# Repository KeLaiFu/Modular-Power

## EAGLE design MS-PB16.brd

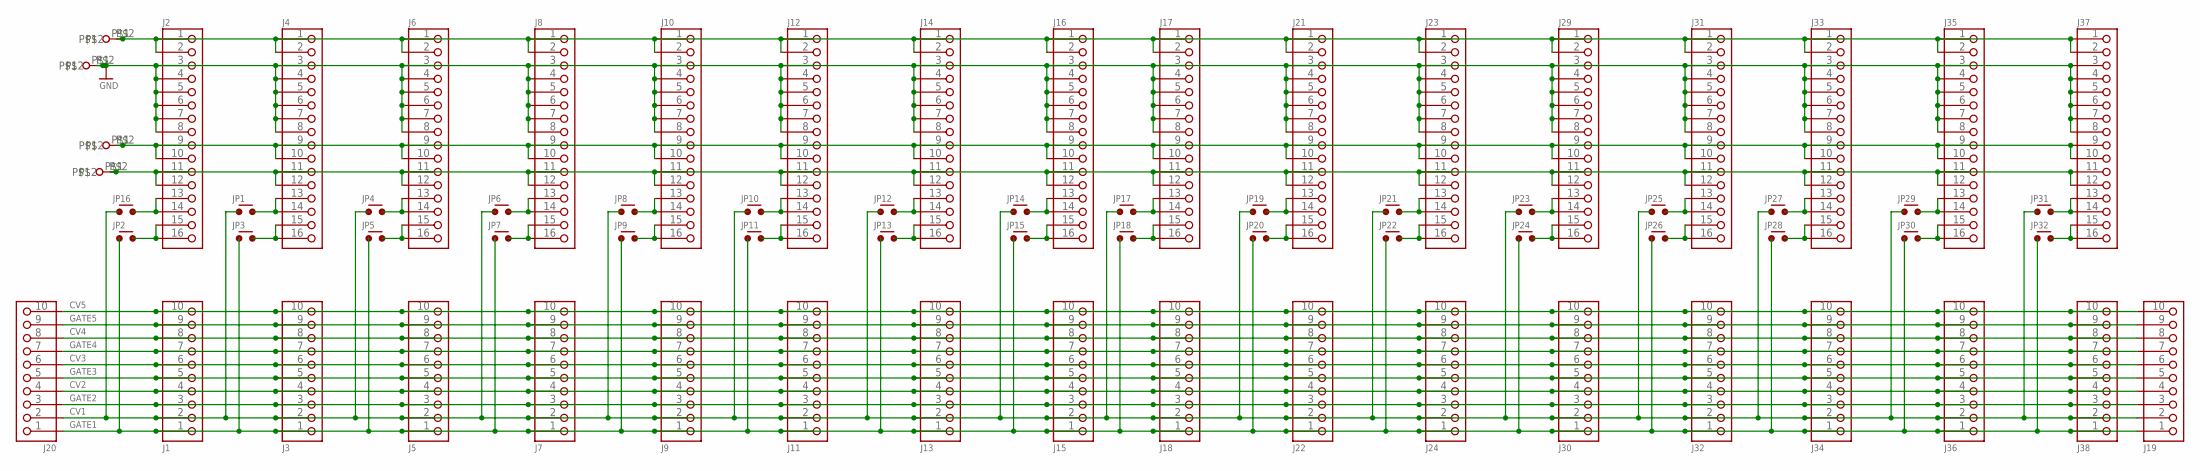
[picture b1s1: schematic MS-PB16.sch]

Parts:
J1, J3, J5, J7, J9, J11, J13, J15, J18, J19, J20, J22, J24, J30, J32, J34, J36, J38: CON10PD_S; PD10S
J2, J4, J6, J8, J10, J12, J14, J16, J17, J21, J23, J29, J31, J33, J35, J37: CON16_PDS; PD16S
J25, J26, J27, J28: FLACHSTECKER-6,35
JP1, JP2, JP3, JP4, JP5, JP6, JP7, JP8, JP9, JP10, JP11, JP12, JP13, JP14, JP15, JP16, JP17, JP18, JP19, JP20, JP21, JP22, JP23, JP24, JP25, JP26, JP27, JP28, JP29, JP30, JP31, JP32: JUMP2J2; JUMP2

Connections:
+5V: J2.11, J2.12, J4.11, J4.12, J6.11, J6.12, J8.11, J8.12, J10.11, J10.12, J12.11, J12.12, J14.11, J14.12, J16.11, J16.12, J17.11, J17.12, J21.11, J21.12, J23.11, J23.12, J27.P$1, J27.P$2, J29.11, J29.12, J31.11, J31.12, J33.11, J33.12, J35.11, J35.12, J37.11, J37.12
+12V: J2.9, J2.10, J4.9, J4.10, J6.9, J6.10, J8.9, J8.10, J10.9, J10.10, J12.9, J12.10, J14.9, J14.10, J16.9, J16.10, J17.9, J17.10, J21.9, J21.10, J23.9, J23.10, J26.P$1, J26.P$2, J29.9, J29.10, J31.9, J31.10, J33.9, J33.10, J35.9, J35.10, J37.9, J37.10
-12V: J2.1, J2.2, J4.1, J4.2, J6.1, J6.2, J8.1, J8.2, J10.1, J10.2, J12.1, J12.2, J14.1, J14.2, J16.1, J16.2, J17.1, J17.2, J21.1, J21.2, J23.1, J23.2, J25.P$1, J25.P$2, J29.1, J29.2, J31.1, J31.2, J33.1, J33.2, J35.1, J35.2, J37.1, J37.2
CV1: J1.2, J3.2, J5.2, J7.2, J9.2, J11.2, J13.2, J15.2, J18.2, J19.2, J20.2, J22.2, J24.2, J30.2, J32.2, J34.2, J36.2, J38.2, JP1.1, JP4.1, JP6.1, JP8.1, JP10.1, JP12.1, JP14.1, JP16.1, JP17.1, JP19.1, JP21.1, JP23.1, JP25.1, JP27.1, JP29.1, JP31.1
CV2: J1.4, J3.4, J5.4, J7.4, J9.4, J11.4, J13.4, J15.4, J18.4, J19.4, J20.4, J22.4, J24.4, J30.4, J32.4, J34.4, J36.4, J38.4
CV3: J1.6, J3.6, J5.6, J7.6, J9.6, J11.6, J13.6, J15.6, J18.6, J19.6, J20.6, J22.6, J24.6, J30.6, J32.6, J34.6, J36.6, J38.6
CV4: J1.8, J3.8, J5.8, J7.8, J9.8, J11.8, J13.8, J15.8, J18.8, J19.8, J20.8, J22.8, J24.8, J30.8, J32.8, J34.8, J36.8, J38.8
CV5: J1.10, J3.10, J5.10, J7.10, J9.10, J11.10, J13.10, J15.10, J18.10, J19.10, J20.10, J22.10, J24.10, J30.10, J32.10, J34.10, J36.10, J38.10
GATE1: J1.1, J3.1, J5.1, J7.1, J9.1, J11.1, J13.1, J15.1, J18.1, J19.1, J20.1, J22.1, J24.1, J30.1, J32.1, J34.1, J36.1, J38.1, JP2.1, JP3.1, JP5.1, JP7.1, JP9.1, JP11.1, JP13.1, JP15.1, JP18.1, JP20.1, JP22.1, JP24.1, JP26.1, JP28.1, JP30.1, JP32.1
GATE2: J1.3, J3.3, J5.3, J7.3, J9.3, J11.3, J13.3, J15.3, J18.3, J19.3, J20.3, J22.3, J24.3, J30.3, J32.3, J34.3, J36.3, J38.3
GATE3: J1.5, J3.5, J5.5, J7.5, J9.5, J11.5, J13.5, J15.5, J18.5, J19.5, J20.5, J22.5, J24.5, J30.5, J32.5, J34.5, J36.5, J38.5
GATE4: J1.7, J3.7, J5.7, J7.7, J9.7, J11.7, J13.7, J15.7, J18.7, J19.7, J20.7, J22.7, J24.7, J30.7, J32.7, J34.7, J36.7, J38.7
GATE5: J1.9, J3.9, J5.9, J7.9, J9.9, J11.9, J13.9, J15.9, J18.9, J19.9, J20.9, J22.9, J24.9, J30.9, J32.9, J34.9, J36.9, J38.9
GND: J2.3, J2.4, J2.5, J2.6, J2.7, J2.8, J4.3, J4.4, J4.5, J4.6, J4.7, J4.8, J6.3, J6.4, J6.5, J6.6, J6.7, J6.8, J8.3, J8.4, J8.5, J8.6, J8.7, J8.8, J10.3, J10.4, J10.5, J10.6, J10.7, J10.8, J12.3, J12.4, J12.5, J12.6, J12.7, J12.8, J14.3, J14.4, J14.5, J14.6, J14.7, J14.8, J16.3, J16.4, J16.5, J16.6, J16.7, J16.8, J17.3, J17.4, J17.5, J17.6, J17.7, J17.8, J21.3, J21.4, J21.5, J21.6, J21.7, J21.8, J23.3, J23.4, J23.5, J23.6, J23.7, J23.8, J28.P$1, J28.P$2, J29.3, J29.4, J29.5, J29.6, J29.7, J29.8, J31.3, J31.4, J31.5, J31.6, J31.7, J31.8, J33.3, J33.4, J33.5, J33.6, J33.7, J33.8, J35.3, J35.4, J35.5, J35.6, J35.7, J35.8, J37.3, J37.4, J37.5, J37.6, J37.7, J37.8
unnamed: J4.13, J4.14, JP1.2
unnamed: J2.15, J2.16, JP2.2
unnamed: J2.13, J2.14, JP16.2
unnamed: J4.15, J4.16, JP3.2
unnamed: J6.13, J6.14, JP4.2
unnamed: J6.15, J6.16, JP5.2
unnamed: J8.15, J8.16, JP7.2
unnamed: J8.13, J8.14, JP6.2
unnamed: J10.13, J10.14, JP8.2
unnamed: J10.15, J10.16, JP9.2
unnamed: J12.13, J12.14, JP10.2
unnamed: J12.15, J12.16, JP11.2
unnamed: J14.13, J14.14, JP12.2
unnamed: J14.15, J14.16, JP13.2
unnamed: J16.13, J16.14, JP14.2
unnamed: J16.15, J16.16, JP15.2
unnamed: J17.13, J17.14, JP17.2
unnamed: J17.15, J17.16, JP18.2
unnamed: J21.13, J21.14, JP19.2
unnamed: J21.15, J21.16, JP20.2
unnamed: J23.13, J23.14, JP21.2
unnamed: J23.15, J23.16, JP22.2
unnamed: J29.13, J29.14, JP23.2
unnamed: J29.15, J29.16, JP24.2
unnamed: J31.13, J31.14, JP25.2
unnamed: J31.15, J31.16, JP26.2
unnamed: J33.13, J33.14, JP27.2
unnamed: J33.15, J33.16, JP28.2
unnamed: J35.13, J35.14, JP29.2
unnamed: J35.15, J35.16, JP30.2
unnamed: J37.13, J37.14, JP31.2
unnamed: J37.15, J37.16, JP32.2

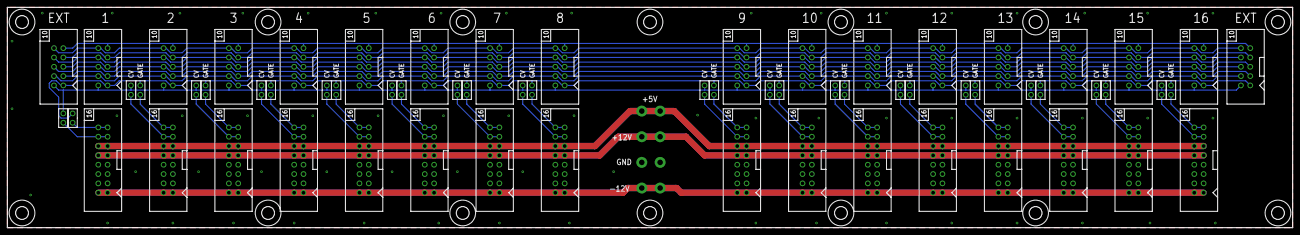
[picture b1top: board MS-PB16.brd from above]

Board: 2 copper layers, 350.0 x 60.0 mm, 85 parts (0 on the bottom side), 46 nets.

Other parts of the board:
U$1, U$2, U$4, U$5, U$6, U$7, U$23, U$24, U$26, U$27, U$28, U$29, U$31, U$32: BF3,5
U$21: LEA-MASK

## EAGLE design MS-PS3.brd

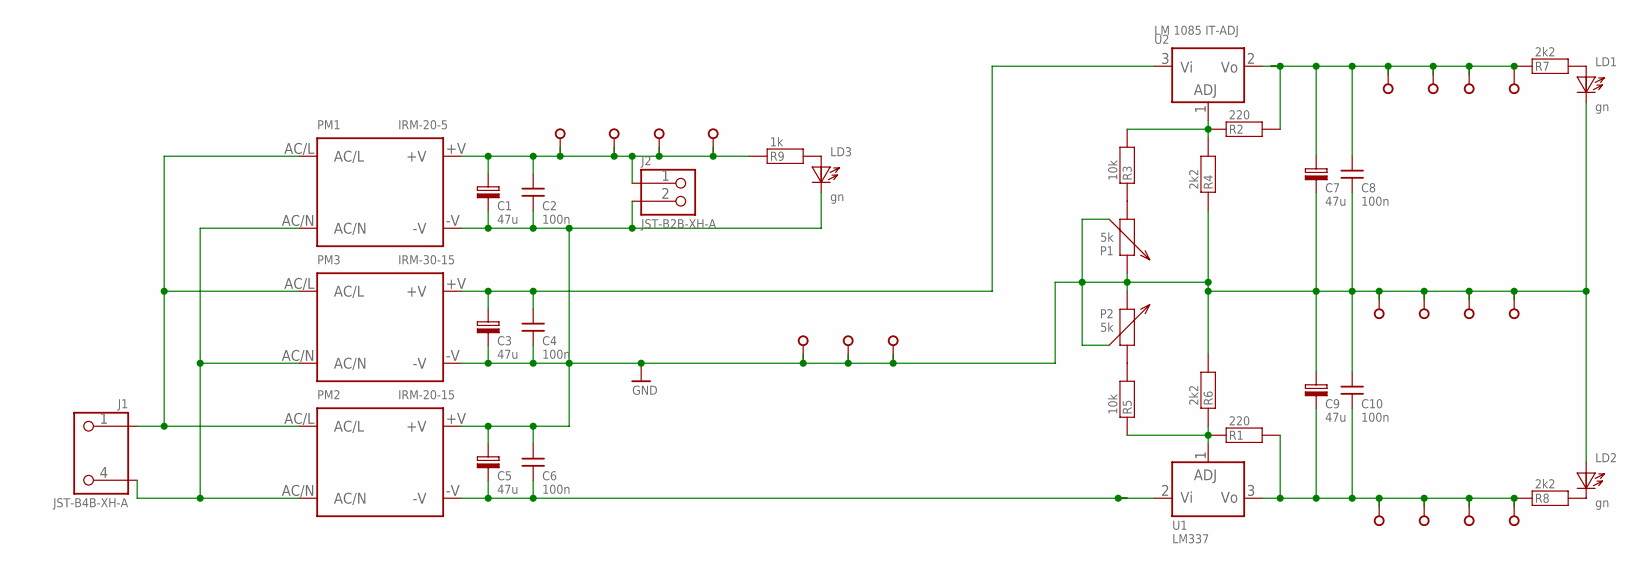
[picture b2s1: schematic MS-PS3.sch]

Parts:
C1, C3, C5, C7, C9: 47u; ES2,5X6,3
C2, C4, C6, C8, C10: 100n; K5-2,5
J1: JST-B4B-XH-A; JST-B4B-XH-A-HV
J2: JST-B2B-XH-A
J3, J4, J5, J6, J7, J8, J9, J10, J11, J12, J13, J14, J15, J16, J17, J18, J19, J20, J21: FLACHSTECKER-6,35
LD1, LD2, LD3: gn; LED3
P1, P2: 5k; POT-25-64Y
PM1: IRM-20-5; IRM-20
PM2: IRM-20-15; IRM-20
PM3: IRM-30-15; IRM-30
R1, R2: 220; R-7,5
R3, R5: 10k; R-7,5
R4, R6, R7, R8: 2k2; R-7,5
R9: 1k; R-7,5
U1: LM337; TO-220N
U2: LM 1085 IT-ADJ; TO-220N
U$5, U$7: SK65; SK65-37,5

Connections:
+12V: C7.1, C8.1, J9.P$1, J9.P$2, J10.P$1, J10.P$2, J11.P$1, J11.P$2, J12.P$1, R2.2, R7.1, U2.2 (VO), U$7.P$1, U$7.P$2
-15V: C5.2, C6.2, PM2.-V, U1.2 (VI), U$5.P$1, U$5.P$2
GND: C1.2, C2.2, C3.2, C4.2, C5.1, C6.1, C7.2, C8.2, C9.1, C10.1, J2.2, J7.P$1, J7.P$2, J8.P$1, J8.P$2, J13.P$1, J13.P$2, J14.P$1, J14.P$2, J15.P$1, J15.P$2, J16.P$1, J16.P$2, J21.P$1, J21.P$2, LD1.K, LD2.A, LD3.K, P1.2, P1.3, P2.2, P2.3, PM1.-V, PM2.+V, PM3.-V, R4.1, R6.2
unnamed: J1.4, PM1.AC/N, PM2.AC/N, PM3.AC/N
unnamed: J1.1, PM1.AC/L, PM2.AC/L, PM3.AC/L
unnamed: R1.1, R5.1, R6.1, U1.1 (ADJ)
unnamed: R2.1, R3.2, R4.2, U2.1 (ADJ)
unnamed: LD1.A, R7.2
unnamed: LD2.K, R8.2
unnamed: P2.1, R5.2
unnamed: C3.1, C4.1, PM3.+V, U2.3 (VI)
unnamed: P1.1, R3.1
unnamed: LD3.A, R9.2
unnamed: C9.2, C10.2, J17.P$1, J17.P$2, J18.P$1, J18.P$2, J19.P$1, J19.P$2, J20.P$1, J20.P$2, R1.2, R8.1, U1.3 (VO)
unnamed: C1.1, C2.1, J2.1, J3.P$1, J3.P$2, J4.P$1, J4.P$2, J5.P$1, J5.P$2, J6.P$1, J6.P$2, PM1.+V, R9.1

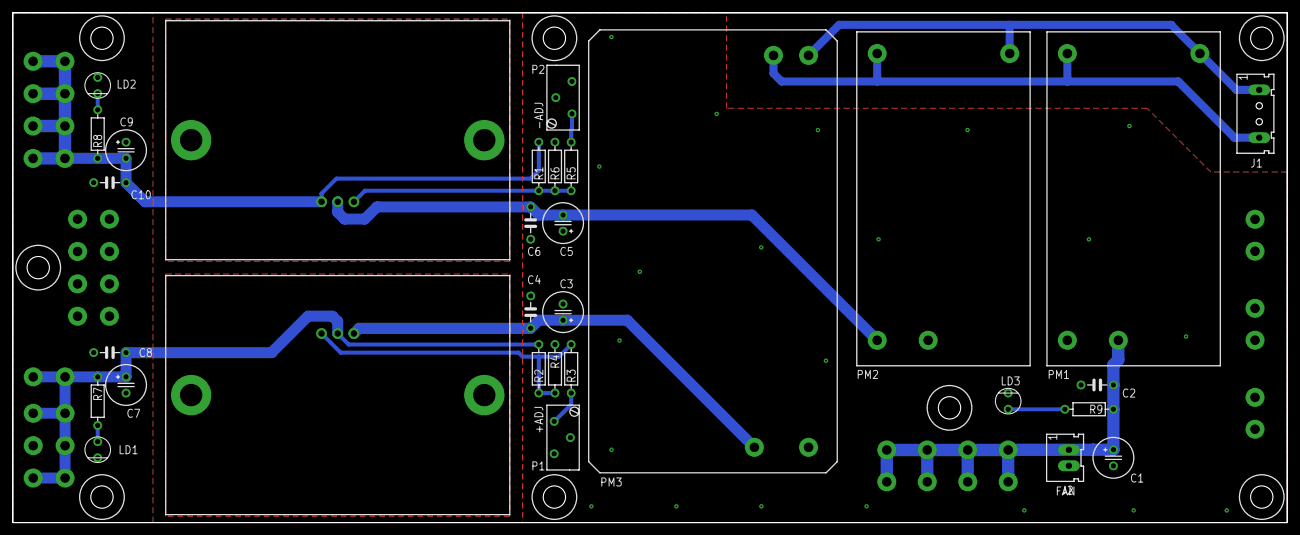
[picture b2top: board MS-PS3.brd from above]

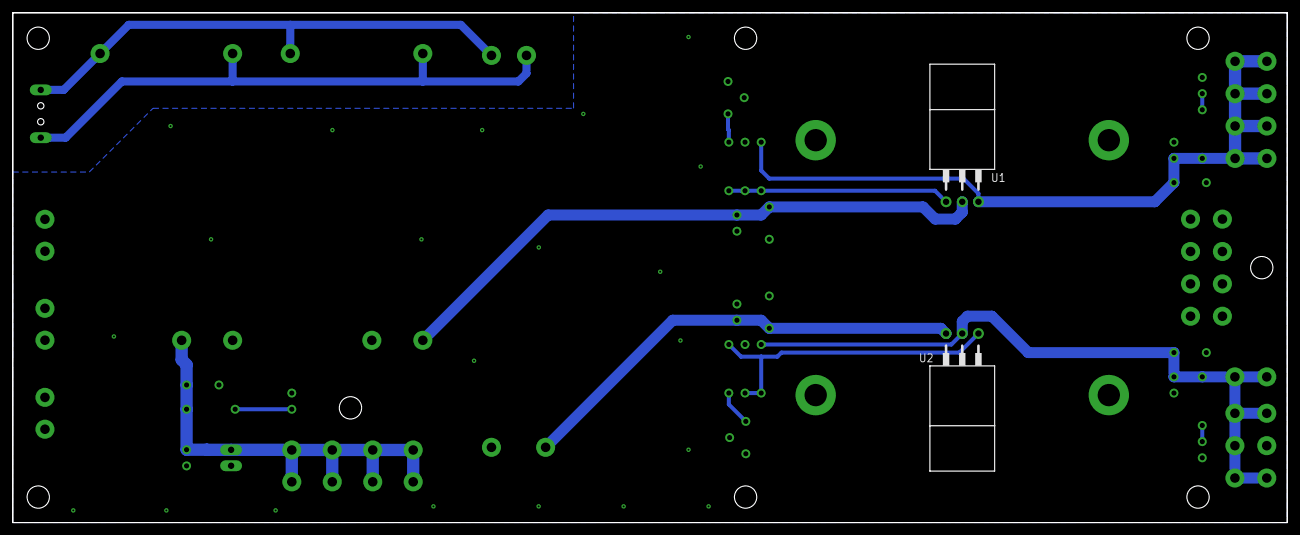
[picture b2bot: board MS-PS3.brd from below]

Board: 2 copper layers, 200.0 x 80.0 mm, 61 parts (2 on the bottom side), 15 nets.

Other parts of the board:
U$1, U$31, U$32, U$33, U$34, U$35, U$36, U$37: BF3,5
U$25: LEA-MASK

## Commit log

2020-05-29 Add files via upload
    zip files are gerplots for jlcpcb
2020-05-29 Add files via upload
    .brd Eagle board file
    .sch Eagle schematic file
